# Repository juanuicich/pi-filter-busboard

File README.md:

# Low-Noise Eurorack Busboard (37cm)

An open-source, high-integrity power distribution busboard for Eurorack modular synthesizer systems. It features aggressive passive filtering designed specifically to clean up the switching and regulation ripple from standard industrial switched-mode power supplies (such as the Mean Well LRS-75-12).

## Features

- **37cm Long Layout:** Optimized for physical accessibility across 84hp cases without needing to uninstall central modules to change power cables.
- **Third-Order CLC Pi-Filter:** Achieves ~35dB of noise attenuation at 1kHz, eliminating audible regulation ripple and high-frequency switching hash (65kHz+).
- **Optional +5V Sub-System:** Includes an unpopulated TO-220 footprint compatible with high-efficiency switching buck regulators (e.g., Murata OKI-78SR-5) to drive 5V-enabled IDC headers locally.
- **LED Rail Indicators:** Post-filter diagnostic LEDs immediately confirm active voltage delivery to the distribution rail.

## Filter & Power Specifications

- **Input Terminals:** 3-pin screw terminal block (5.08mm pitch, Phoenix Contact standard).
- **Maximum Current Load:** 2A - 2.5A continuous per board.
- **Input Capacitors ($C_{in}$):** 220µF / 25V+ Low-ESR Electrolytic ($\le$ 0.1Ω impedance at 100kHz).
- **Series Inductors ($L$):** 330µH Toroidal Chokes ($\ge$ 3A rated, low DCR).
- **Output Capacitors ($C_{out}$):** 4700µF / 25V Low-ESR Electrolytic ($\le$ 0.03Ω impedance at 100kHz).

## Critical Assembly & Solder Notes

⚠️ **WARNING: REVERSE POLARITY HAZARD**
Electrolytic capacitors are polarized. On the **-12V rail**, Ground (0V) is the more positive potential. You **MUST** solder the positive lead (+) of the -12V capacitors directly to the Ground plane, and the negative lead (-) to the -12V trace. Installing them backward will cause the capacitors to burst violently upon power-up.

- **Thermal Reliefs:** Ensure your KiCad zone properties retain thermal relief spokes for through-hole pads, otherwise the massive output capacitors and ground planes will sink all the heat from your soldering iron.
- **Mechanical Security:** Because the 4700µF output capacitors carry significant mass, it is recommended to apply a small dab of non-conductive electronics-grade silicone or hot glue between the base of the capacitor capacitor body and the PCB after soldering to relieve trace stress during case transit.

## License

This project is open-source hardware. Feel free to modify, build, or manufacture your own variants.

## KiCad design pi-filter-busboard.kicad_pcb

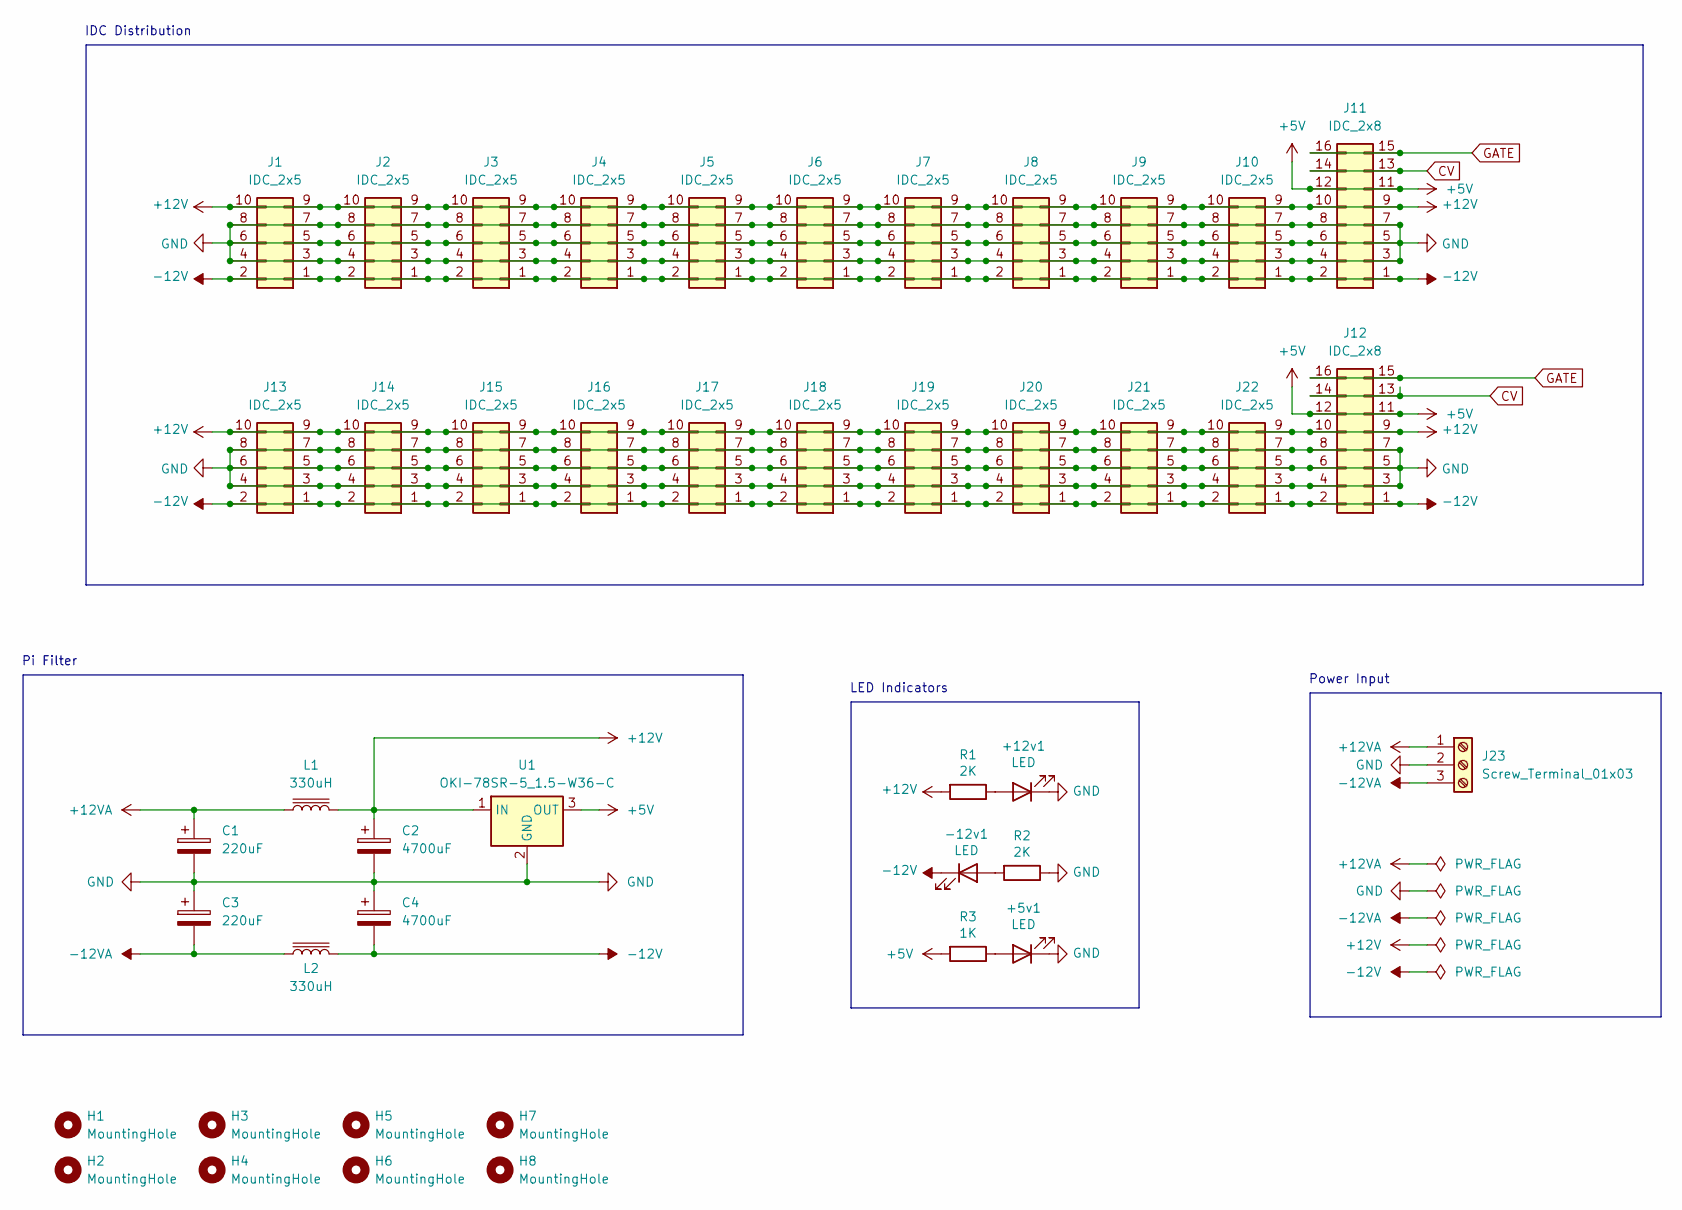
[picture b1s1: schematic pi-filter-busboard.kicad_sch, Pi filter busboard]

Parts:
+5v1, +12v1: LED; LED_D3.0mm
-12v1: LED; LED_D3.0mm
C1, C3: 220uF; CP_Radial_D8.0mm_P3.50mm
C2, C4: 4700uF; CP_Radial_D16.0mm_P7.50mm
H1, H2, H3, H4, H5, H6, H7, H8: MountingHole; MountingHole_3.2mm_M3
J1, J2, J3, J4, J5, J6, J7, J8, J9, J10, J13, J14, J15, J16, J17, J18, J19, J20, J21, J22: IDC_2x5; IDC-Header_2x05_P2.54mm_Vertical
J11, J12: IDC_2x8; IDC-Header_2x08_P2.54mm_Vertical
J23: Screw_Terminal_01x03; TerminalBlock_RND_205-00002_1x03_P5.00mm_Horizontal
L1, L2: 330uH; L_Toroid_Vertical_L21.6mm_W9.1mm_P8.40mm_Bourns_5700
R1, R2: 2K; R_Axial_DIN0207_L6.3mm_D2.5mm_P7.62mm_Horizontal
R3: 1K; R_Axial_DIN0207_L6.3mm_D2.5mm_P7.62mm_Horizontal
U1: OKI-78SR-5_1.5-W36-C; Converter_DCDC_Murata_OKI-78SR_Vertical

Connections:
+5V: J11.11, J11.12, J12.11, J12.12, R3.2, U1.3 (OUT)
+12V: C2.1, J1.9, J1.10, J2.9, J2.10, J3.9, J3.10, J4.9, J4.10, J5.9, J5.10, J6.9, J6.10, J7.9, J7.10, J8.9, J8.10, J9.9, J9.10, J10.9, J10.10, J11.9, J11.10, J12.9, J12.10, J13.9, J13.10, J14.9, J14.10, J15.9, J15.10, J16.9, J16.10, J17.9, J17.10, J18.9, J18.10, J19.9, J19.10, J20.9, J20.10, J21.9, J21.10, J22.9, J22.10, L1.2, R1.2, U1.1 (IN)
+12VA: C1.1, J23.1, L1.1
-12V: -12v1.1 (K), C4.2, J1.1, J1.2, J2.1, J2.2, J3.1, J3.2, J4.1, J4.2, J5.1, J5.2, J6.1, J6.2, J7.1, J7.2, J8.1, J8.2, J9.1, J9.2, J10.1, J10.2, J11.1, J11.2, J12.1, J12.2, J13.1, J13.2, J14.1, J14.2, J15.1, J15.2, J16.1, J16.2, J17.1, J17.2, J18.1, J18.2, J19.1, J19.2, J20.1, J20.2, J21.1, J21.2, J22.1, J22.2, L2.2; also elsewhere on the board
-12VA: C3.2, J23.3, L2.1
CV: J11.13, J11.14, J12.13, J12.14
GATE: J11.15, J11.16, J12.15, J12.16
GND: +5v1.1 (K), +12v1.1 (K), C1.2, C2.2, C3.1, C4.1, J1.3, J1.4, J1.5, J1.6, J1.7, J1.8, J2.3, J2.4, J2.5, J2.6, J2.7, J2.8, J3.3, J3.4, J3.5, J3.6, J3.7, J3.8, J4.3, J4.4, J4.5, J4.6, J4.7, J4.8, J5.3, J5.4, J5.5, J5.6, J5.7, J5.8, J6.3, J6.4, J6.5, J6.6, J6.7, J6.8, J7.3, J7.4, J7.5, J7.6, J7.7, J7.8, J8.3, J8.4, J8.5, J8.6, J8.7, J8.8, J9.3, J9.4, J9.5, J9.6, J9.7, J9.8, J10.3, J10.4, J10.5, J10.6, J10.7, J10.8, J11.3, J11.4, J11.5, J11.6, J11.7, J11.8, J12.3, J12.4, J12.5, J12.6, J12.7, J12.8, J13.3, J13.4, J13.5, J13.6, J13.7, J13.8, J14.3, J14.4, J14.5, J14.6, J14.7, J14.8, J15.3, J15.4, J15.5, J15.6, J15.7, J15.8, J16.3, J16.4, J16.5, J16.6, J16.7, J16.8, J17.3, J17.4, J17.5, J17.6, J17.7, J17.8, J18.3, J18.4, J18.5, J18.6, J18.7, J18.8, J19.3, J19.4, J19.5, J19.6, J19.7, J19.8, J20.3, J20.4, J20.5, J20.6, J20.7, J20.8, J21.3, J21.4, J21.5, J21.6, J21.7, J21.8, J22.3, J22.4, J22.5, J22.6, J22.7, J22.8, J23.2, R2.1, U1.2 (GND); also elsewhere on the board
unnamed 8: +5v1.2 (A), R3.1; also elsewhere on the board
unnamed 9: +12v1.2 (A), R1.1; also elsewhere on the board
unnamed 10: -12v1.2 (A), R2.2; also elsewhere on the board

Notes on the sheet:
LED Indicators
Power Input
IDC Distribution
Pi Filter

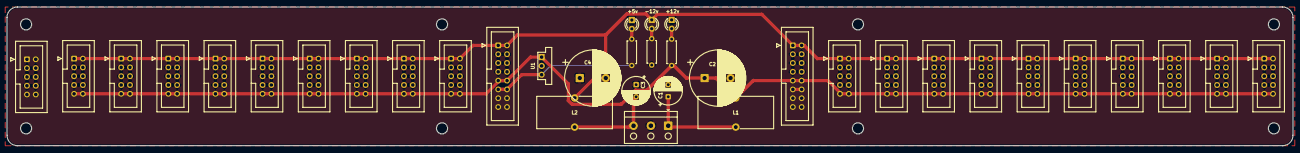
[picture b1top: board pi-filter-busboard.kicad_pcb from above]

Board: 2 copper layers, 371.0 x 40.0 mm, 44 parts (0 on the bottom side), 11 nets.

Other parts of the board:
+5v, +12v: LED; LED_D3.0mm
-12v: LED; LED_D3.0mm

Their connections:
-12V: -12v.1 (K); also elsewhere on the board
GND: +5v.1 (K), +12v.1 (K); also elsewhere on the board
unnamed 8: +5v.2 (A); also elsewhere on the board
unnamed 9: +12v.2 (A); also elsewhere on the board
unnamed 10: -12v.2 (A); also elsewhere on the board
